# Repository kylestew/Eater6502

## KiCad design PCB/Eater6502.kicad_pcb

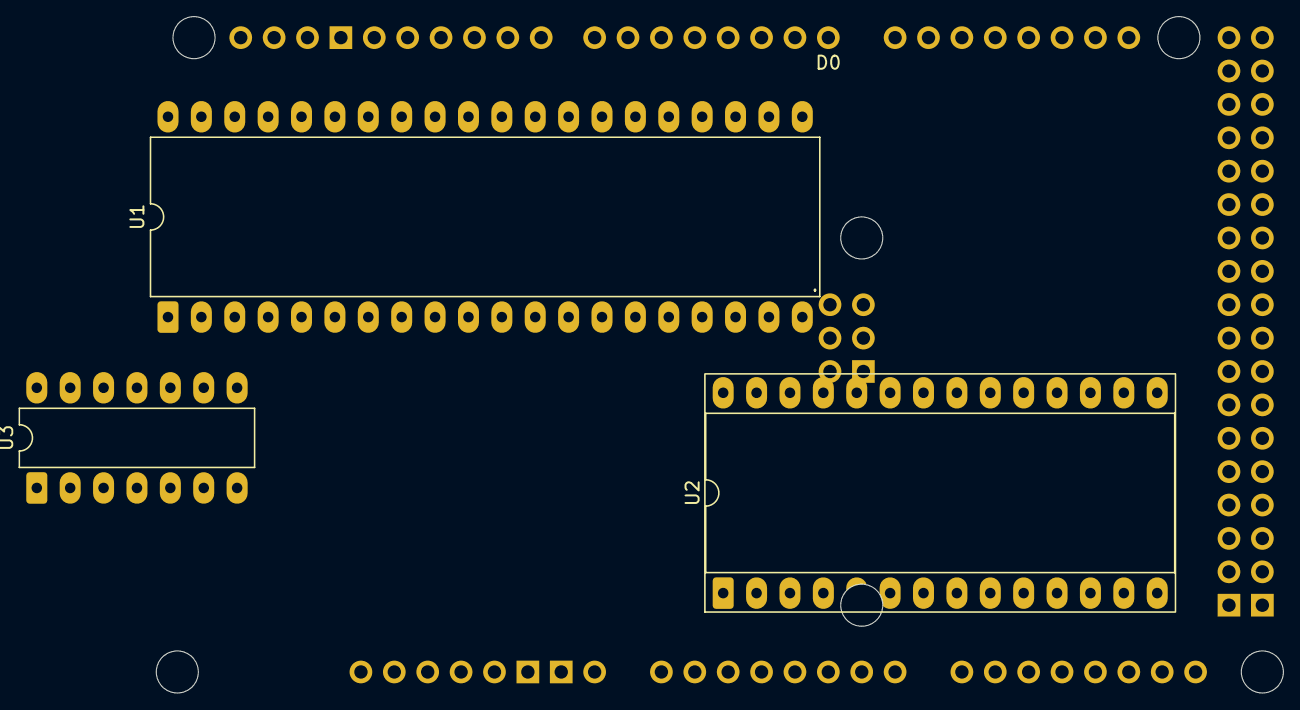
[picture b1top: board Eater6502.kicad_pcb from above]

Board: 2 copper layers, 4 parts (0 on the bottom side), 19 nets, no tracks yet.

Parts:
A1: Arduino_Mega2560_R3_Shield
U1: W65C02S; DIP-40_W15.24mm_LongPads
U2: 28C256; DIP-28_W15.24mm_Socket_LongPads
U3: 74HC00; DIP-14_W7.62mm_LongPads

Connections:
+5V: A1.5V1 (5V), A1.5V3 (5V), A1.5V4 (5V), U1.4 (~IRQ), U1.6 (~NMI), U1.8 (VDD), U1.36 (BE), U1.38 (~SO), U2.27 (~WE), U2.28 (VCC), U3.14 (VCC)
/A0: U1.9 (A0), U2.10 (A0)
/A1: U1.10 (A1), U2.9 (A1)
/A2: U1.11 (A2), U2.8 (A2)
/A3: U1.12 (A3), U2.7 (A3)
/A4: U1.13 (A4), U2.6 (A4)
/A5: U1.14 (A5), U2.5 (A5)
/A6: U1.15 (A6), U2.4 (A6)
/A7: U1.16 (A7), U2.3 (A7)
/A8: U1.17 (A8), U2.25 (A8)
/A9: U1.18 (A9), U2.24 (A9)
/A10: U1.19 (A10), U2.21 (A10)
/A11: U1.20 (A11), U2.23 (A11)
/A12: U1.22 (A12), U2.2 (A12)
/A13: U1.23 (A13), U2.26 (A13)
/A14: U1.24 (A14), U2.1 (A14)
/A15: U1.25 (A15), U3.12, U3.13
GND: A1.GND1 (GND), A1.GND2 (GND), A1.GND3 (GND), A1.GND5 (GND), A1.GND6 (GND), U1.21 (VSS), U2.14 (GND), U2.22 (~OE), U3.7 (GND)
unnamed: U2.20 (~CS), U3.11

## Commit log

2025-11-25 Working on firmware for debugging
2025-11-29 Working debugger and firmware for store to address
2025-12-30 Hardcode data mode
2026-01-02 Fix debug code to read data lines right
2026-01-02 OBSERVE on clock high bud
2026-01-07 Modes and fixes
2026-01-08 RAM working code
